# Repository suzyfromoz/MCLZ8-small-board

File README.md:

# MCLZ8-small-board
A small interface board between a Teensy 4.1 and a Z80 socket to run MCLZ8 code

Two boards are presented - MCLZ8_PCB fits in the same footprint as The Teensy 4.1 and performs the functionality of @MicroCoreLabs MCLZ8 board, in providing the bus buffering for the Teensy. The Schematic is unchanged from @MicroCoreLabs MCLZ8. The 40 pin probing adapter B board goes underneath, and simply adapts the 40 pin header from the first board back to 0.6" hole centers, so we can plug it into a Z80 socket.

The MCLZ8_PCB is four layers, while the probing adapter board is two.

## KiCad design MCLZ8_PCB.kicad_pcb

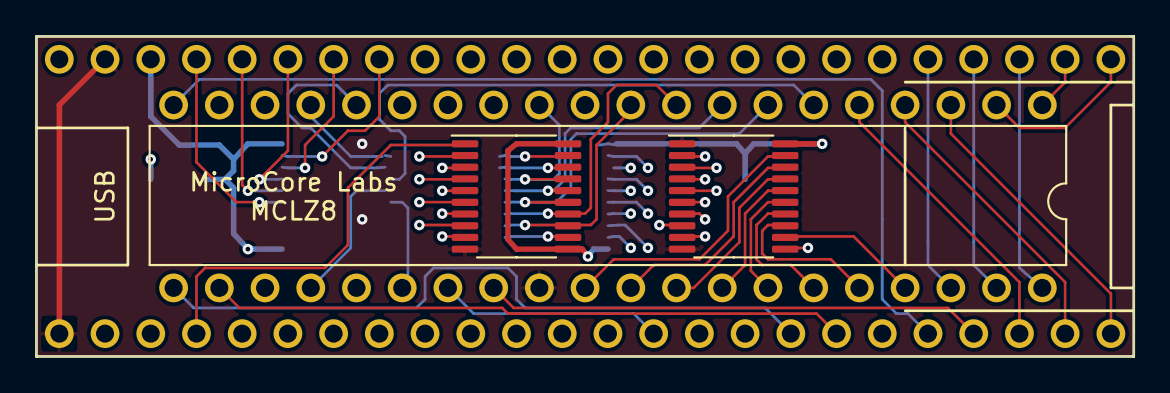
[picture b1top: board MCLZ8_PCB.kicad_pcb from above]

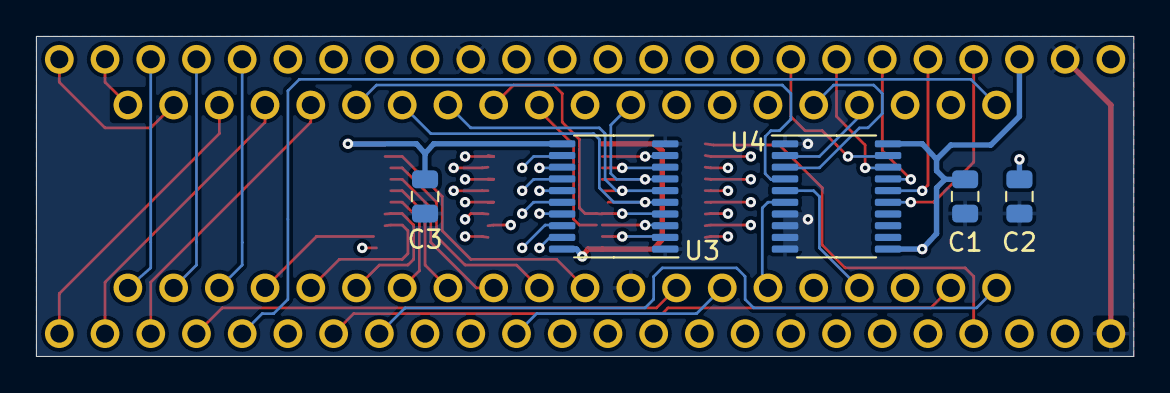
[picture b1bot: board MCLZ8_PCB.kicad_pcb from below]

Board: 4 copper layers, 61.0 x 17.8 mm, 9 parts (5 on the bottom side), 62 nets.

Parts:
C1, C2, C3: 100n; C_0805_2012Metric
U1: Teensy4.1; Teensy41_Ted_Modified
U3, U4, U5, U7: SN74LVC573A; TSSOP-20_4.4x6.5mm_P0.65mm
U6: Z80CPU; DIP-40_W15.24mm

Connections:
+3V3: C1.1, C3.1, U1.15 (3V3), U1.46 (3V3), U3.11 (Load), U3.20 (VCC), U4.11 (Load), U4.20 (VCC), U5.11 (Load), U5.20 (VCC), U7.20 (VCC)
+5V: C2.1, U1.48 (VIN), U6.11 (VCC)
CPU_A0: U6.30 (A0), U7.19 (Q0)
CPU_A1: U6.31 (A1), U7.18 (Q1)
CPU_A2: U6.32 (A2), U7.17 (Q2)
CPU_A3: U6.33 (A3), U7.16 (Q3)
CPU_A4: U6.34 (A4), U7.15 (Q4)
CPU_A5: U6.35 (A5), U7.14 (Q5)
CPU_A6: U6.36 (A6), U7.13 (Q6)
CPU_A7: U6.37 (A7), U7.12 (Q7)
CPU_A8: U1.29 (37_CS), U6.38 (A8)
CPU_A9: U1.28 (36_CS), U6.39 (A9)
CPU_A10: U1.27 (35_TX8), U6.40 (A10)
CPU_A11: U1.26 (34_RX8), U6.1 (A11)
CPU_A12: U1.25 (33_MCLK2), U6.2 (A12)
CPU_A13: U1.24 (32_OUT1B), U6.3 (A13)
CPU_A14: U1.23 (31_CTX3), U6.4 (A14)
CPU_A15: U1.22 (30_CRX3), U6.5 (A15)
CPU_AD0: U3.9 (D7), U5.19 (Q0), U6.14 (D0)
CPU_AD1: U3.8 (D6), U5.18 (Q1), U6.15 (D1)
CPU_AD2: U3.7 (D5), U5.17 (Q2), U6.12 (D2)
CPU_AD3: U3.6 (D4), U5.16 (Q3), U6.8 (D3)
CPU_AD4: U3.5 (D3), U5.15 (Q4), U6.7 (D4)
CPU_AD5: U3.4 (D2), U5.14 (Q5), U6.9 (D5)
CPU_AD6: U3.3 (D1), U5.13 (Q6), U6.10 (D6)
CPU_AD7: U3.2 (D0), U5.12 (Q7), U6.13 (D7)
CPU_CLK: U4.4 (D2), U6.6 (~CLK)
CPU_HALT: U1.16 (24_A10_TX6_SCL2), U6.18 (~HALT)
CPU_INTR: U4.3 (D1), U6.16 (~INT)
CPU_IOREQ: U1.20 (28_RX7), U6.20 (~IORQ)
CPU_M1: U1.14 (12_MISO_MQSL), U6.27 (~M1)
CPU_MREQ: U1.19 (27_A13_SCK1), U6.19 (~MREQ)
CPU_NMI: U4.2 (D0), U6.17 (~NMI)
CPU_RD: U1.17 (25_A11_RX6_SDA2), U6.21 (~RD)
CPU_REFRESH: U1.21 (29_TX7), U6.28 (~RFSH)
CPU_RESET: U4.6 (D4), U6.26 (~RESET)
CPU_WAIT: U4.5 (D3), U6.24 (~WAIT)
CPU_WR: U1.18 (26_A12_MOSI1), U6.22 (~WR)
GND: C1.2, C2.2, C3.2, U1.1 (GND), U1.34 (GND), U1.47 (GND), U3.1 (OE), U3.10 (GND), U4.1 (OE), U4.7 (D5), U4.8 (D6), U4.9 (D7), U4.10 (GND), U5.10 (GND), U6.29 (GND), U7.1 (OE), U7.10 (GND)
TEENSY_AD0_IN: U1.40 (18_A4_SDA), U3.12 (Q7)
TEENSY_AD0_OUT: U1.5 (3_LRCLK2), U5.2 (D0), U7.2 (D0)
TEENSY_AD1_IN: U1.39 (17_A3_TX4_SDA1), U3.13 (Q6)
TEENSY_AD1_OUT: U1.6 (4_BCLK2), U5.3 (D1), U7.3 (D1)
TEENSY_AD2_IN: U1.38 (16_A2_RX4_SCL1), U3.14 (Q5)
TEENSY_AD2_OUT: U1.7 (5_IN2), U5.4 (D2), U7.4 (D2)
TEENSY_AD3_IN: U1.37 (15_A1_RX3_SPDIF_IN), U3.15 (Q4)
TEENSY_AD3_OUT: U1.8 (6_OUT1D), U5.5 (D3), U7.5 (D3)
TEENSY_AD4_IN: U1.36 (14_A0_TX3_SPDIF_OUT), U3.16 (Q3)
TEENSY_AD4_OUT: U1.9 (7_RX2_OUT1A), U5.6 (D4), U7.6 (D4)
TEENSY_AD5_IN: U1.33 (41_A17), U3.17 (Q2)
TEENSY_AD5_OUT: U1.10 (8_TX2_IN1), U5.7 (D5), U7.7 (D5)
TEENSY_AD6_IN: U1.32 (40_A16), U3.18 (Q1)
TEENSY_AD6_OUT: U1.11 (9_OUT1C), U5.8 (D6), U7.8 (D6)
TEENSY_AD7_IN: U1.31 (39_MISO1_OUT1A), U3.19 (Q0)
TEENSY_AD7_OUT: U1.12 (10_CS_MQSR), U5.9 (D7), U7.9 (D7)
TEENSY_ADDR_LATCH_n: U1.13 (11_MOSI_CTX1), U7.11 (Load)
TEENSY_CLK: U1.43 (21_A7_RX5_BCLK1), U4.17 (Q2)
TEENSY_DATA_OE_n: U1.4 (2_OUT2), U5.1 (OE)
TEENSY_INTR: U1.42 (20_A6_TX5_LRCLK1), U4.18 (Q1)
TEENSY_NMI: U1.41 (19_A5_SCL), U4.19 (Q0)
TEENSY_RESET: U1.45 (23_A9_CRX1_MCLK1), U4.15 (Q4)
TEENSY_WAIT: U1.44 (22_A8_CTX1), U4.16 (Q3)
